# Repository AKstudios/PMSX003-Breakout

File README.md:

# PMSX003-Breakout
This is a breakout for the 8 pin connector for PMS5003/7003 PM2.5 sensor. All necessary pins are broken out

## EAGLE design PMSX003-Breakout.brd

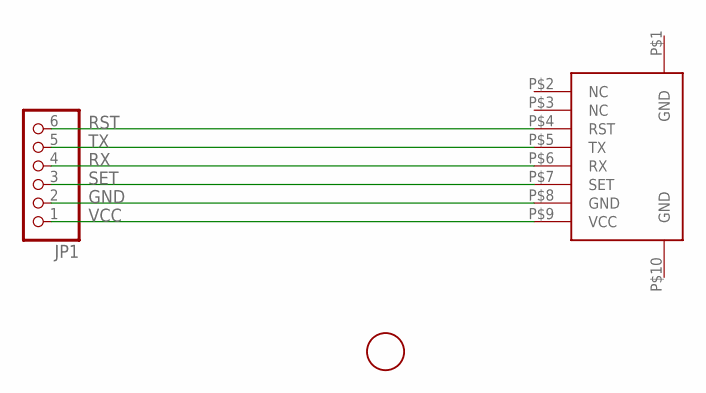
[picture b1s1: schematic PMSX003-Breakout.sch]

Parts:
JP1: PINHD-1X6; 1X06
U$1: 0532610871
U$2: FIDUCIAL; FIDUCIAL_1MM

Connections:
GND: JP1.2, U$1.P$8 (GND)
RST: JP1.6, U$1.P$4 (RST)
RX: JP1.4, U$1.P$6 (RX)
SET: JP1.3, U$1.P$7 (SET)
TX: JP1.5, U$1.P$5 (TX)
VCC: JP1.1, U$1.P$9 (VCC)

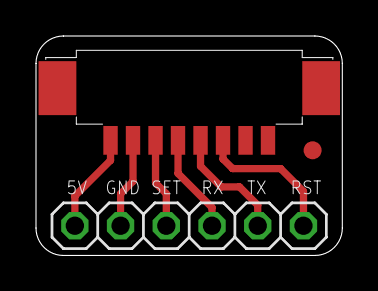
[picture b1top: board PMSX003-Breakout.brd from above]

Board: 2 copper layers, 17.0 x 12.2 mm, 3 parts (0 on the bottom side), 6 nets.

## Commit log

2017-04-17 :space_invader: Added .gitattributes & .gitignore files
2017-04-17 Added EAGLE files
2017-04-17 Minor update
